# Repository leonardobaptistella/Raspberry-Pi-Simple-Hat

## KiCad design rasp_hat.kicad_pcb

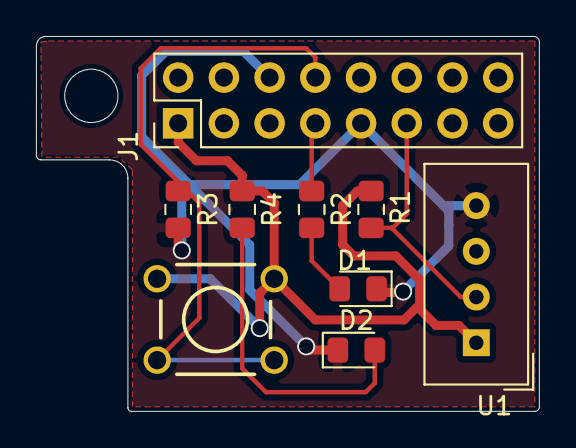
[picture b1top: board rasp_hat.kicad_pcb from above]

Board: 2 copper layers, 27.9 x 20.8 mm, 9 parts (0 on the bottom side), 7 nets.

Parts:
D1, D2: LED; LED_0805_2012Metric_Pad1.15x1.40mm_HandSolder
J1: Raspberry_Pi_2_3; PinHeader_2x08_P2.54mm_Vertical
R1, R4: 330; R_0805_2012Metric_Pad1.15x1.40mm_HandSolder
R2, R3: 10K; R_0805_2012Metric_Pad1.15x1.40mm_HandSolder
SW1: SW_DPST; SW_PUSHBUTTON_PTH
U1: DHT22; Aosong_DHT11_5.5x12.0_P2.54mm

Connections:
+3V3: J1.1, R2.2, R4.1, SW1.1, U1.1
GND: D1.1, D2.1, J1.6, J1.9, R3.2, U1.4
unnamed: D1.2, R1.2
unnamed: D2.2, R4.2
unnamed: J1.7, R1.1
unnamed: J1.11, R2.1, U1.2
gpio14: J1.8, R3.1, SW1.2

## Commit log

2021-03-15 Version 1.0
